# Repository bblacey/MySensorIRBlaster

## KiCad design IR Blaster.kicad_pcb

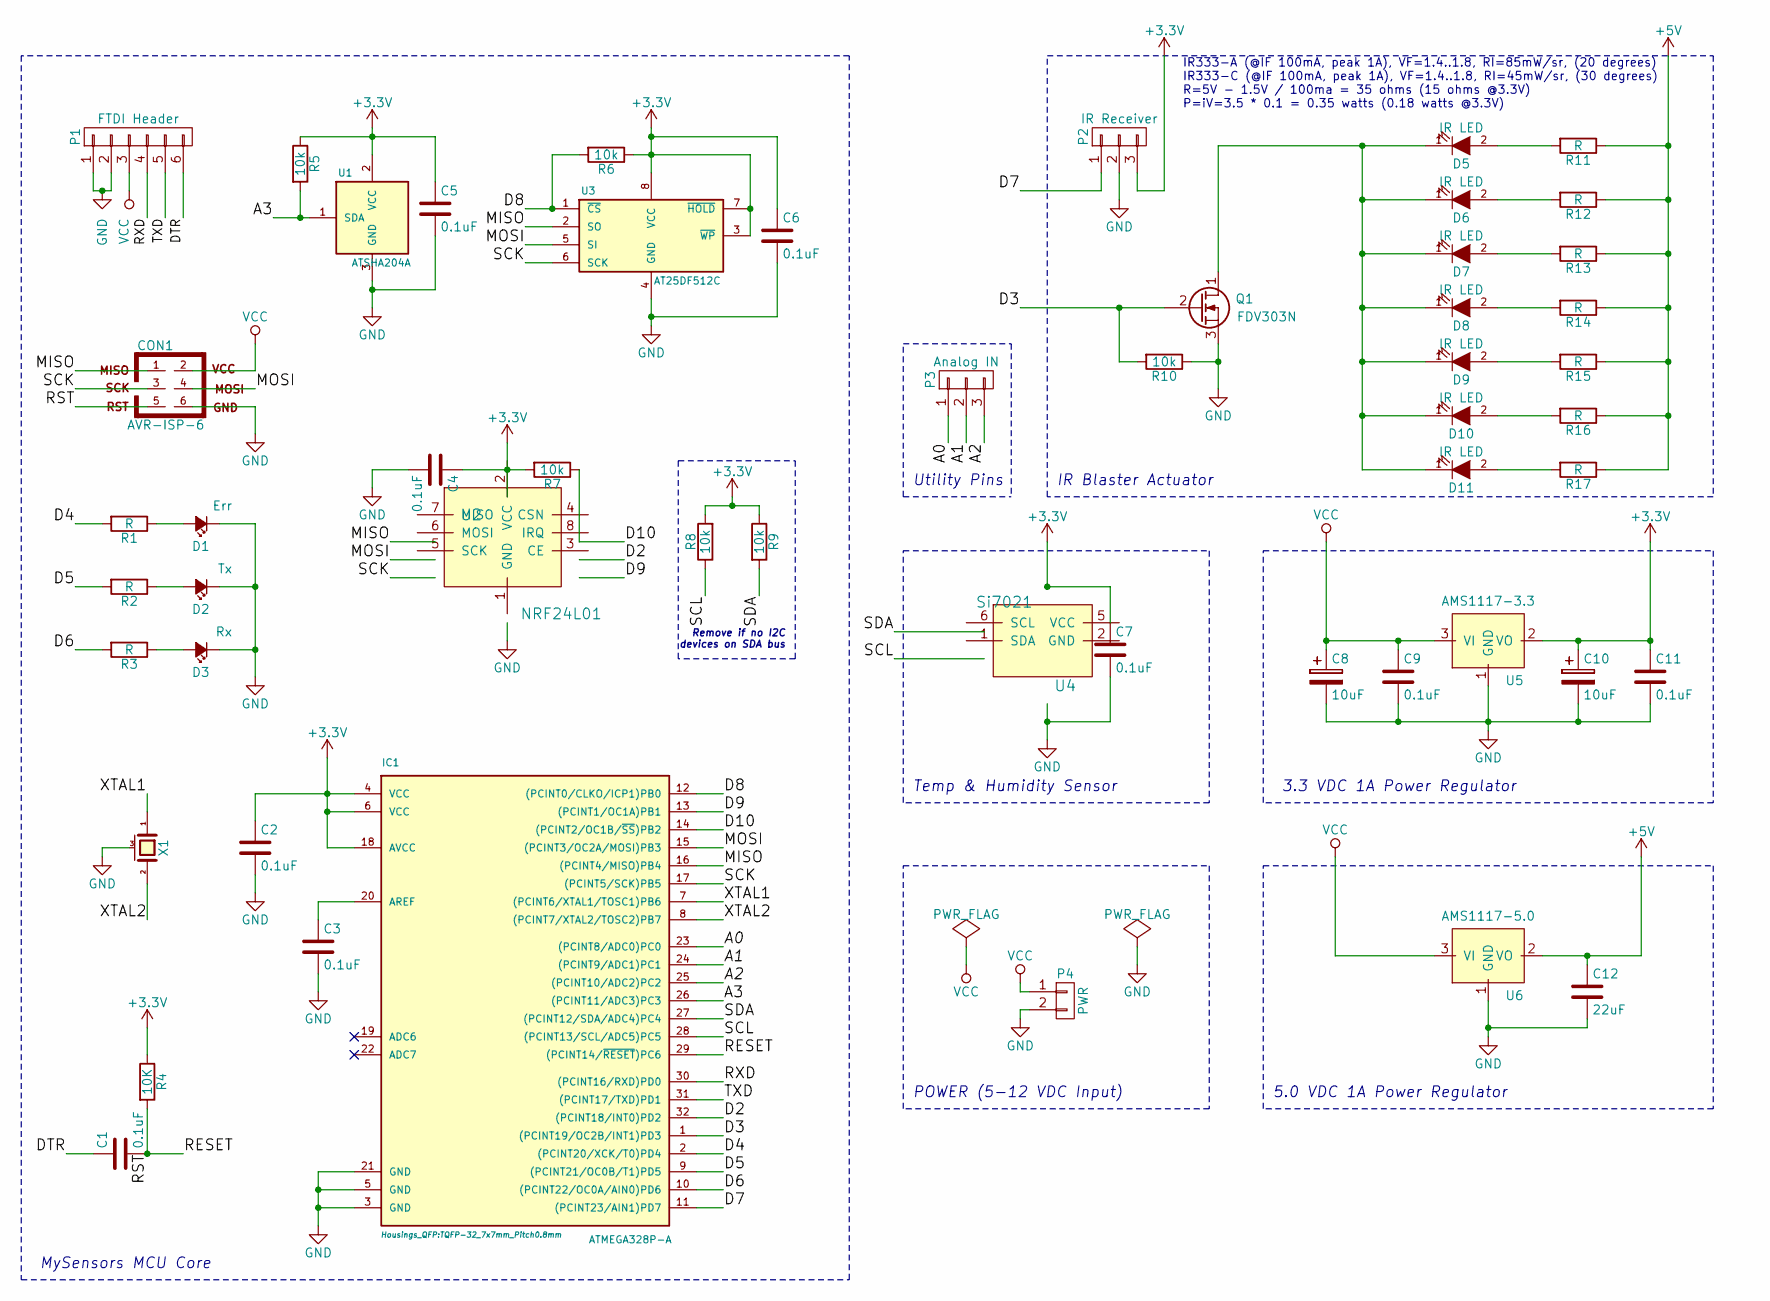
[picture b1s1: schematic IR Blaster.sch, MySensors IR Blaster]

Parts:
C1, C2, C3, C4, C5, C6, C7, C9, C11: 0.1uF; C_0603
C8, C10: 10uF; C_0603
C12: 22uF; C_0603
CON1: AVR-ISP-6; Socket_Strip_Straight_2x03
D1: Err; LED-0603
D2: Tx; LED-0603
D3: Rx; LED-0603
D5, D6, D7, D8, D9, D10, D11: IR LED; LED-5MM-Horizontal
IC1: ATMEGA328P-A; TQFP-32_7x7mm_Pitch0.8mm
P1: FTDI Header; Pin_Header_Straight_1x06
P2: IR Receiver; Socket_Strip_Straight_1x03
P3: Analog IN; Pin_Header_Straight_1x03
P4: PWR; TerminalBlock2.54mmx2-kcswalter
Q1: FDV303N; SOT-23
R1, R2, R3, R11, R12, R13, R14, R15, R16, R17: R; R_0603
R4: 10K; R_0603
R5, R6, R7, R8, R9, R10: 10k; R_0603
U1: ATSHA204A; SOT-23
U2: NRF24L01
U3: AT25DF512C; SOIC-8_3.9x4.9mm_Pitch1.27mm
U4: Si7021; DFN-6-1EP_3x3mm_Pitch0.95mm
U5: AMS1117-3.3; SOT-223
U6: AMS1117-5.0; SOT-223
X1: CRYSTAL; crystal_FA238-TSX3225

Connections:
+3V3: C2.1, C4.1, C5.1, C6.1, C7.1, C10.1, C11.1, IC1.4 (VCC), IC1.6 (VCC), IC1.18 (AVCC), P2.3, R4.1, R5.1, R6.1, R7.2, R8.2, R9.1, U1.2 (VCC), U2.2 (VCC), U3.3 (~WP), U3.7 (~HOLD), U3.8 (VCC), U4.5 (VCC), U5.2 (VO)
+5V: C12.1, R11.1, R12.1, R13.1, R14.1, R15.1, R16.1, R17.1, U6.2 (VO)
/A0: IC1.23 ((PCINT8/ADC0)PC0), P3.1
/A1: IC1.24 ((PCINT9/ADC1)PC1), P3.2
/A2: IC1.25 ((PCINT10/ADC2)PC2), P3.3
/A3: IC1.26 ((PCINT11/ADC3)PC3), R5.2, U1.1 (SDA)
/D2: IC1.32 ((PCINT18/INT0)PD2), U2.8 (IRQ)
/D3: IC1.1 ((PCINT19/OC2B/INT1)PD3), Q1.2 (G), R10.2
/D4: IC1.2 ((PCINT20/XCK/T0)PD4), R1.2
/D5: IC1.9 ((PCINT21/OC0B/T1)PD5), R2.2
/D6: IC1.10 ((PCINT22/OC0A/AIN0)PD6), R3.2
/D7: IC1.11 ((PCINT23/AIN1)PD7), P2.1
/D8: IC1.12 ((PCINT0/CLKO/ICP1)PB0), R6.2, U3.1 (~CS)
/D9: IC1.13 ((PCINT1/OC1A)PB1), U2.3 (CE)
/D10: IC1.14 ((PCINT2/OC1B/~SS~)PB2), R7.1, U2.4 (CSN)
/DTR: C1.1, P1.6
/MISO: CON1.1, IC1.16 ((PCINT4/MISO)PB4), U2.7 (MISO), U3.2 (SO)
/MOSI: CON1.4, IC1.15 ((PCINT3/OC2A/MOSI)PB3), U2.6 (MOSI), U3.5 (SI)
/RESET: C1.2, CON1.5, IC1.29 ((PCINT14/~RESET~)PC6), R4.2
/RXD: IC1.30 ((PCINT16/RXD)PD0), P1.4
/SCK: CON1.3, IC1.17 ((PCINT5/SCK)PB5), U2.5 (SCK), U3.6 (SCK)
/SCL: IC1.28 ((PCINT13/SCL/ADC5)PC5), R8.1, U4.6 (SCL)
/SDA: IC1.27 ((PCINT12/SDA/ADC4)PC4), R9.2, U4.1 (SDA)
/TXD: IC1.31 ((PCINT17/TXD)PD1), P1.5
/XTAL1: IC1.7 ((PCINT6/XTAL1/TOSC1)PB6), X1.1
/XTAL2: IC1.8 ((PCINT7/XTAL2/TOSC2)PB7), X1.2
GND: C2.2, C3.2, C4.2, C5.2, C6.2, C7.2, C8.2, C9.2, C10.2, C11.2, C12.2, CON1.6, D1.1 (K), D2.1 (K), D3.1 (K), IC1.3 (GND), IC1.5 (GND), IC1.21 (GND), P1.1, P1.2, P2.2, P4.2, Q1.3 (S), R10.1, U1.3 (GND), U2.1 (GND), U3.4 (GND), U4.2 (GND), U5.1 (GND), U6.1 (GND), X1.3 (case)
unnamed: C3.1, IC1.20 (AREF)
unnamed: D1.2 (A), R1.1
unnamed: D2.2 (A), R2.1
unnamed: D3.2 (A), R3.1
unnamed: D5.2 (A), R11.2
unnamed: D6.2 (A), R12.2
unnamed: D7.2 (A), R13.2
unnamed: D8.2 (A), R14.2
unnamed: D9.2 (A), R15.2
unnamed: D5.1 (K), D6.1 (K), D7.1 (K), D8.1 (K), D9.1 (K), D10.1 (K), D11.1 (K), Q1.1 (D)
unnamed: D10.2 (A), R16.2
unnamed: D11.2 (A), R17.2
VCC: C8.1, C9.1, CON1.2, P1.3, P4.1, U5.3 (VI), U6.3 (VI)

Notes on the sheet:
IR333-A (@IF 100mA, peak 1A), VF=1.4..1.8, RI=85mW/sr, (20 degrees) IR333-C (@IF 100mA, peak 1A), VF=1.4..1.8, RI=45mW/sr, (30 degrees) R=5V - 1.5V / 100ma = 35 ohms (15 ohms @3.3V) P=iV=3.5 * 0.1 = 0.35 watts (0.18 watts @3.3V)
3.3 VDC 1A Power Regulator
IR Blaster Actuator
MySensors MCU Core
Temp & Humidity Sensor
Utility Pins
5.0 VDC 1A Power Regulator
POWER (5-12 VDC Input)
Remove if no I2C devices on SDA bus

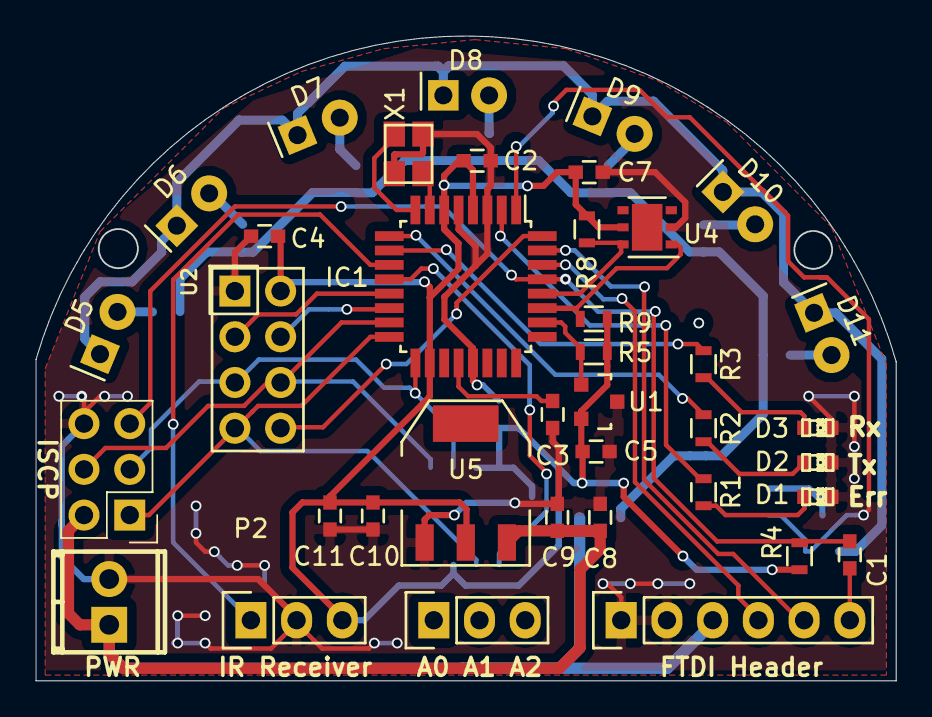
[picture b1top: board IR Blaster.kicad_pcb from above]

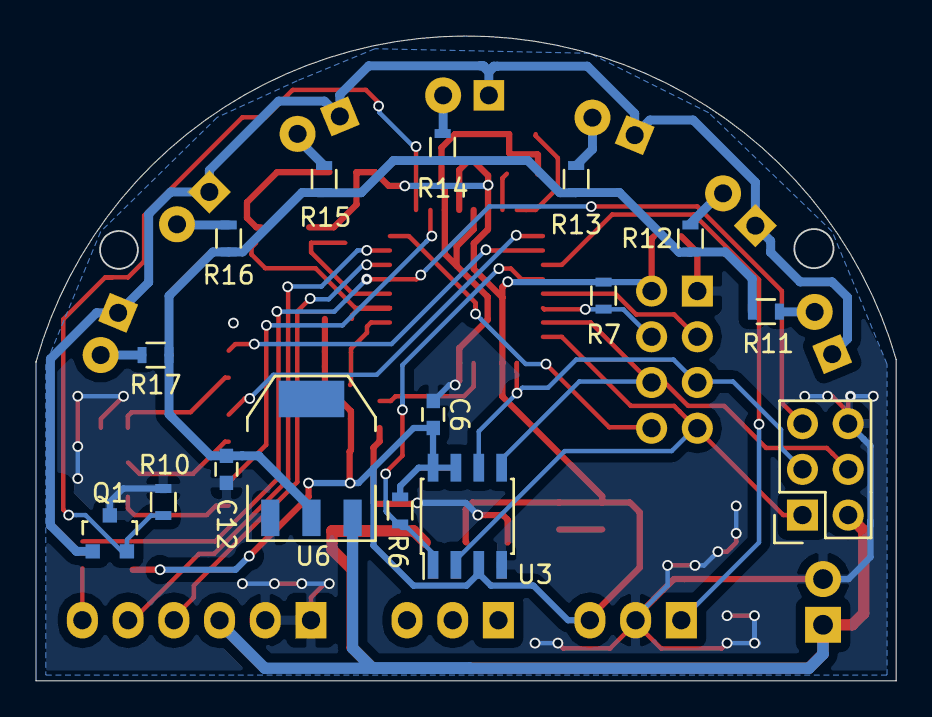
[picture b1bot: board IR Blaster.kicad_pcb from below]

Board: 2 copper layers, 47.7 x 35.7 mm, 53 parts (16 on the bottom side), 40 nets.

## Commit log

2015-06-02 Importing version 0.3 of the IR Blaster KiCad project into git for version management. Currently a 5 LED design dual voltage design.
2015-06-18 Modified design to increase LEDs from 5 @30 degrees to 7 @22.5 degrees to cover 180 degrees with greater distance using narrower angluar displacement IR LEDs. Completed electrical traces except for o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
2015-06-20 General PCB tidying. Added board identifier and OSHW logo, tweaked LED orientation, corrected paths for 3d model view, added top-side silk screen identifiers for connectors, re-oriented ISCP connecto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
2015-06-20 Cleaned up 3D parts (power terminal block and 0603 LEDs) in preparation for v0.4 post and review.
2015-06-24 Project should now be location independent users who have established mysensors part management prequisites as defined on https://github.com/mysensors-kicad/part_management. Implemented MySensors pat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
2015-06-24 Project now uses project-local and writable cow directory and updated to the latest NRF24L01+ footprint and 3d shape.
2015-06-25 Increased higher-current trace widths to ensure ample current to higher-drain parts such as the LEDs.
2015-06-25 Added some modest via stitching to the ground planes.
2015-06-25 Changed references for Walter Lain 3dshapes from personal library to mysensors.3dshapes repo.
2015-06-25 Updated revision from v0.4 to v0.5 for first board run.
2015-06-25 Resolved fab house design requirement violations. "Stitched" vias exceeded minimum drill size for fab house and wider pwr traces were closer to the edge than the minimum allow.
2015-06-25 Added Manufacturing directory following Patrick's convention. This ensures consistent Gerber archive generation for specific fab houses, in this case Smart Prototypes.com
2015-06-25 Added a create_OSHPark.sh Gerber generation script to Manufacturing directory for quick verification of Gerbers and for those users who might prefer to use OSHPark for fabbing.
